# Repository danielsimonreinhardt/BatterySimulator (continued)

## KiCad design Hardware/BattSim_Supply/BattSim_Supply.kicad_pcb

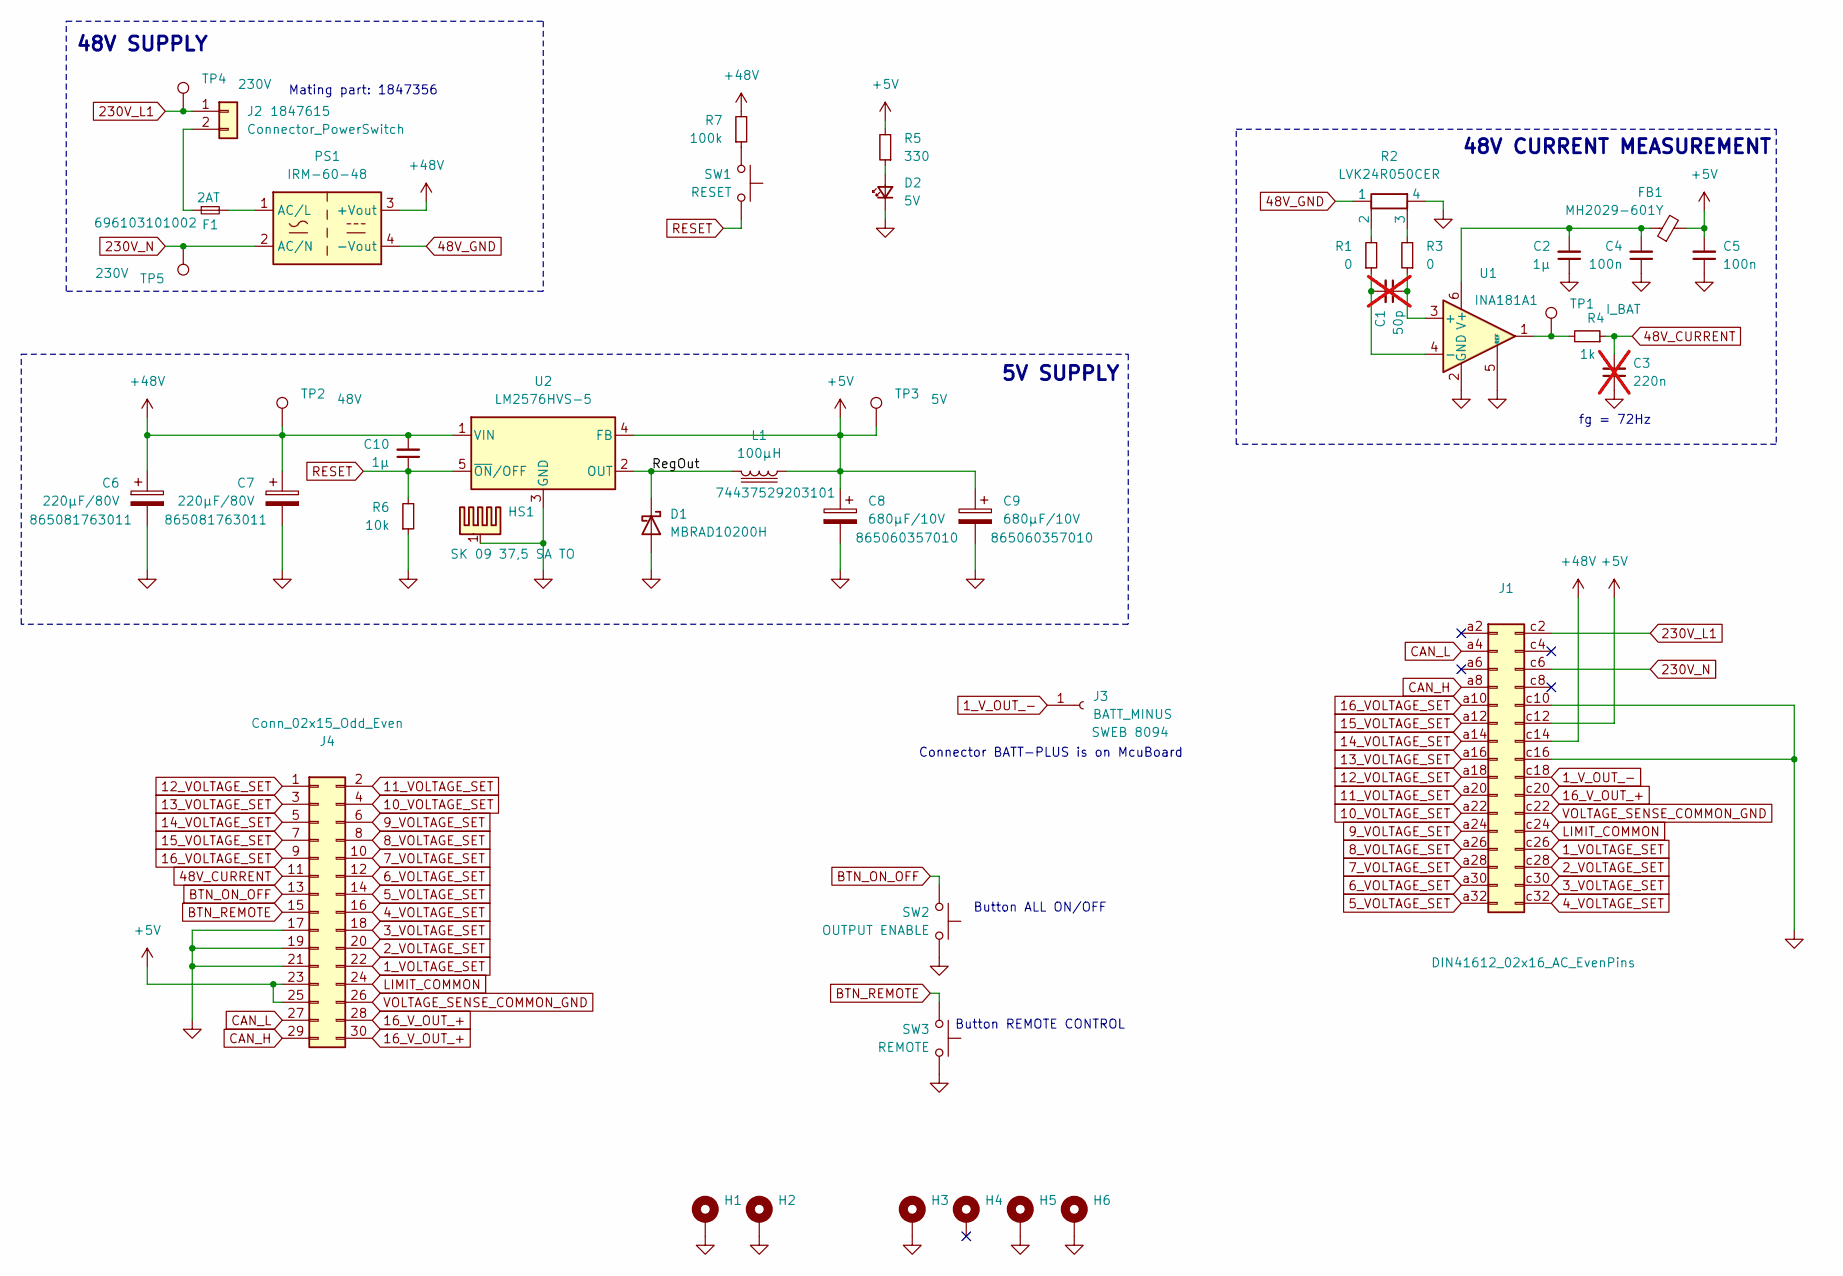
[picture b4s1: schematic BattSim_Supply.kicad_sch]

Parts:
C1: 50p; C_0603_1608Metric_Pad1.08x0.95mm_HandSolder; not fitted
C2, C10: 1µ; C_0603_1608Metric_Pad1.08x0.95mm_HandSolder
C3: 220n; C_0603_1608Metric_Pad1.08x0.95mm_HandSolder; not fitted
C4, C5: 100n; C_0603_1608Metric_Pad1.08x0.95mm_HandSolder
C6, C7: 220µF/80V; CP_Elec_16x17.5
C8, C9: 680µF/10V; CP_Elec_10x10.5
D1: MBRAD10200H; TO-252-2
D2: 5V; LED_D3.0mm_Horizontal_O1.27mm_Z6.0mm
F1: 2AT; Fuseholder_Cylinder-5x20mm_Wuerth_696103101002-SMD_Horizont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
FB1: MH2029-601Y; L_0805_2012Metric_Pad1.05x1.20mm_HandSolder
H1, H2: MountingHole_Pad; MountingHole_2.7mm_M2.5_ISO14580_Pad_TopBottom
H3, H4, H5, H6: MountingHole_Pad; MountingHole_3.2mm_M3_Pad_Via
HS1: SK 09 37,5 SA TO; Heatsink_37,5x29mm_1xFixation3mm_Fischer-SK 09 37,5 SA TO
J1: DIN41612_02x16_AC_EvenPins; DIN41612_C_2x16_Male_Horizontal_THT
J2: Connector_PowerSwitch; PhoenixContact_MCV_1,5_2-GF-5.08_1x02_P5.08mm_Vertical_Thre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
J3: BATT_MINUS; Banana_Cliff_FCR7350B_S16N-PC_Horizontal
J4: Conn_02x15_Odd_Even; PinHeader_2x15_P2.54mm_Vertical
L1: 100µH; L_Wuerth_HCF-2920
PS1: IRM-60-48; Converter_ACDC_MeanWell_IRM-60-xx_THT
R1, R3: 0; R_0603_1608Metric_Pad0.98x0.95mm_HandSolder
R2: LVK24R050CER; R_Shunt_Ohmite_LVK24
R4: 1k; R_0603_1608Metric_Pad0.98x0.95mm_HandSolder
R5: 330; R_0603_1608Metric
R6: 10k; R_0603_1608Metric
R7: 100k; R_0603_1608Metric
SW1: RESET; SW_Tactile_SPST_Angled_PTS645Vx83-2LFS
SW2: OUTPUT ENABLE; SW_Tactile_SPST_Angled_PTS645Vx83-2LFS
SW3: REMOTE; SW_Tactile_SPST_Angled_PTS645Vx83-2LFS
TP1: I_BAT; TestPoint_Pad_D1.0mm
TP2: 48V; TestPoint_Pad_D1.0mm
TP3: 5V; TestPoint_Pad_D1.0mm
TP4, TP5: 230V; TestPoint_Pad_D1.0mm
U1: INA181A1; SOT-23-6
U2: LM2576HVS-5; TO-263-5_TabPin3

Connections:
1_VOLTAGE_SET: J1.c26, J4.22
1_V_OUT_-: J1.c18, J3.1
2_VOLTAGE_SET: J1.c28, J4.20
3_VOLTAGE_SET: J1.c30, J4.18
4_VOLTAGE_SET: J1.c32, J4.16
5_VOLTAGE_SET: J1.a32, J4.14
6_VOLTAGE_SET: J1.a30, J4.12
7_VOLTAGE_SET: J1.a28, J4.10
8_VOLTAGE_SET: J1.a26, J4.8
9_VOLTAGE_SET: J1.a24, J4.6
10_VOLTAGE_SET: J1.a22, J4.4
11_VOLTAGE_SET: J1.a20, J4.2
12_VOLTAGE_SET: J1.a18, J4.1
13_VOLTAGE_SET: J1.a16, J4.3
14_VOLTAGE_SET: J1.a14, J4.5
15_VOLTAGE_SET: J1.a12, J4.7
16_VOLTAGE_SET: J1.a10, J4.9
16_V_OUT_+: J1.c20, J4.28, J4.30
48V_CURRENT: C3.2, J4.11, R4.1
48V_GND: PS1.4 (-Vout), R2.1
230V_L1: J1.c2, J2.1, TP4.1
230V_N: J1.c6, PS1.2 (AC/N), TP5.1
+5V: C5.2, C8.1, C9.1, FB1.2, J1.c12, J4.23, J4.25, L1.1, R5.2, TP3.1, U2.4 (FB)
+48V: C6.1, C7.1, C10.2, J1.c14, PS1.3 (+Vout), R7.2, TP2.1, U2.1 (VIN)
/RegOut: D1.2 (K), L1.2, U2.2 (OUT)
BTN_ON_OFF: J4.13, SW2.2
BTN_REMOTE: J4.15, SW3.2
CAN_H: J1.a8, J4.29
CAN_L: J1.a4, J4.27
GND: C2.1, C3.1, C4.1, C5.1, C6.2, C7.2, C8.2, C9.2, D1.1 (A), D2.1 (K), H1.1, H2.1, H3.1, H5.1, H6.1, HS1.1, J1.c10, J1.c16, J4.17, J4.19, J4.21, R2.4, R6.1, SW2.1, SW3.1, U1.2 (GND), U1.5 (REF), U2.3 (GND)
LIMIT_COMMON: J1.c24, J4.24
unnamed: D2.2 (A), R5.1
unnamed: F1.1, J2.2
unnamed: F1.2, PS1.1 (AC/L)
unnamed: R1.2, R2.2
unnamed: R2.3, R3.2
unnamed: R4.2, TP1.1, U1.1
unnamed: R7.1, SW1.2
unnamed: C1.1, R3.1, U1.3 (+)
unnamed: C1.2, R1.1, U1.4 (-)
unnamed: C2.2, C4.2, FB1.1, U1.6 (V+)
RESET: C10.1, R6.2, SW1.1, U2.5 (~ON/OFF)
VOLTAGE_SENSE_COMMON_GND: J1.c22, J4.26

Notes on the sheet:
48V SUPPLY
fg = 72Hz
Connector BATT-PLUS is on McuBoard
5V SUPPLY
48V CURRENT MEASUREMENT
Mating part: 1847356
Button REMOTE CONTROL
Button ALL ON/OFF

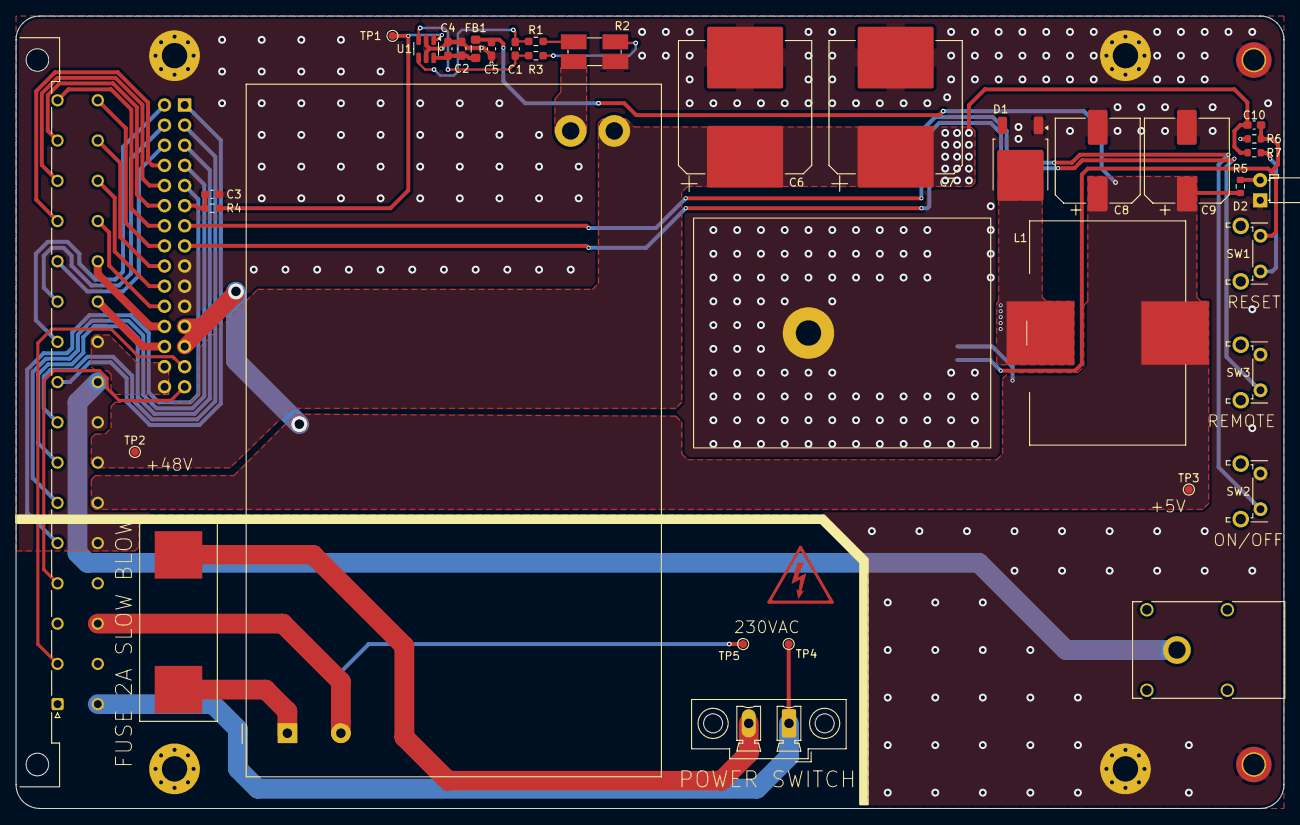
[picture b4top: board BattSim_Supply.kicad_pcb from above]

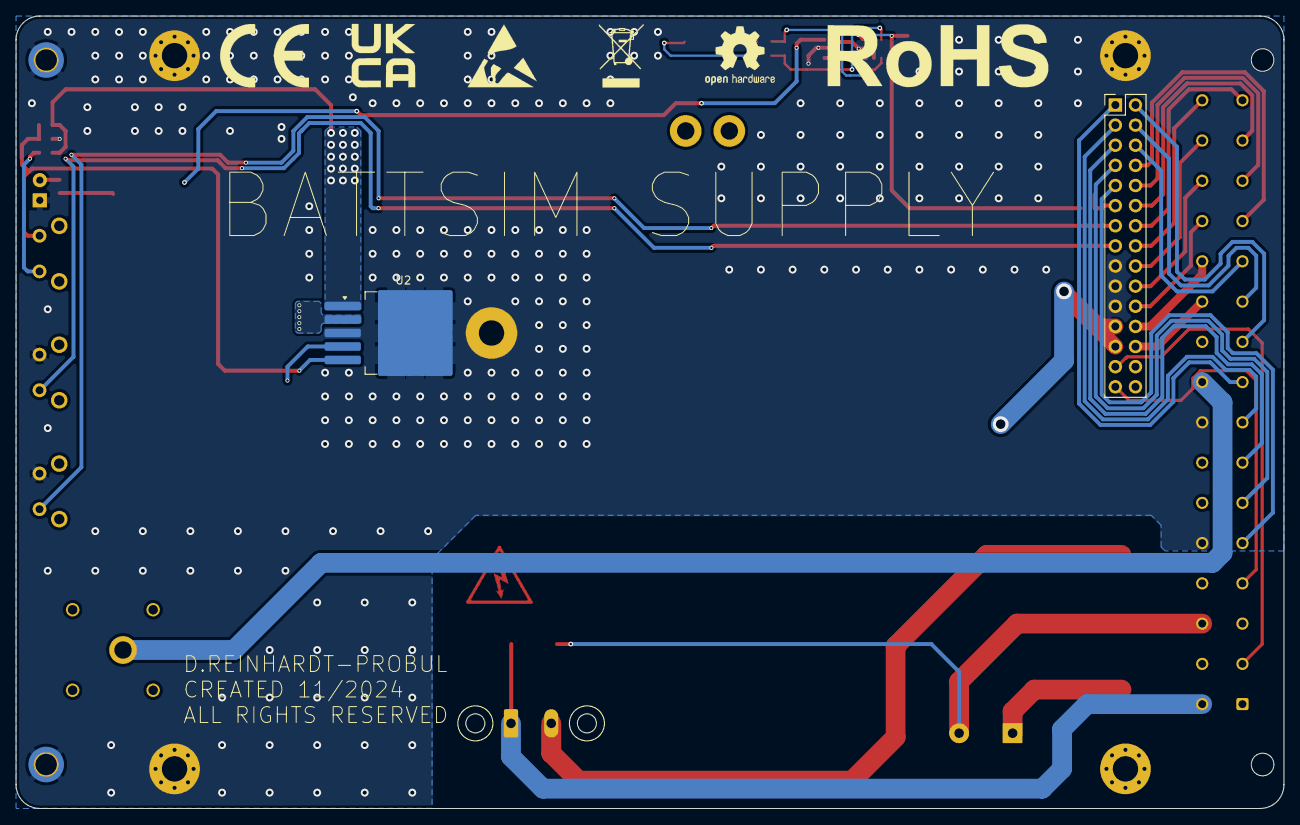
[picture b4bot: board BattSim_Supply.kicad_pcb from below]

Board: 2 copper layers, 160.0 x 100.0 mm, 44 parts (2 on the bottom side), 43 nets.

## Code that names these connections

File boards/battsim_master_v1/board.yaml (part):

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    sda: { pin: PTE15, flexio_pin: 2 }  # [MUX] FlexIO_D2 on PTE15
    scl: { pin: PTE16, flexio_pin: 3, pull: up }  # [MUX] FlexIO_D3 on PTE16; internal pull-up like the factory firmware (IO-125)
    # entered by hand (Studio wizard, step i2c). NO pull-ups on SDA/SCL on the board: [SCH] BattSimMaster.kicad_sch
    # nets DISP_TX/DISP_RX only join J1 (pin 2 = PTE15, pin 3 = PTE16) and the MCU, the MCU pins have none (IO-117). The factory firmware
    # (BATTSIM_CONTROL.slx, device test 2026-11-04) enables the MCU pull-up on SCL only and leaves SDA without; the display worked with that
    # (the module is assumed to hold SDA itself). So SCL gets `pull: up` here and SDA stays without (IO-125).

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    - { name: ST_13, pin: PTB2, active: low, verify: true }
    - { name: ST_14, pin: PTB29, active: low, verify: true }
    - { name: BTN_ALL_ON_OFF, pin: PTD11, active: low, pull: up, verify: true }
    - { name: BTN_REMOTE, pin: PTD12, active: low, pull: up, verify: true }
    - { name: LIMIT, pin: PTE25, active: low, pull: down, verify: true }
    - { name: ENC_VOLT_BTN, pin: PTA25, active: low, pull: up, verify: true }
    - { name: ENC_SEL_BTN, pin: PTA16, active: low, pull: up, verify: true }
  outputs:
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    - { name: SEL_13, pin: PTE2, active: high, verify: true }
    - { name: EN_14, pin: PTD13, active: low, verify: true }
    - { name: SEL_14, pin: PTE19, active: high, verify: true }
    - { name: LED1, pin: PTA11, active: high, verify: true }
    - { name: LED2, pin: PTA12, active: high, verify: true }
    - { name: LED_REMOTE, pin: PTA8, active: high, verify: true }

# No board port was written (ecu/platforms/<board>/Options.cmake). Since ARCH-58 that is not needed to build: the
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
